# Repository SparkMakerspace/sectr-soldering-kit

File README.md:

This PCB was designed by the nerds at [Spark Makerspace](https://sparkmakerspace.org) for use with [Southeastern CT](https://southeasternctrobotics.com/) Robotics (SECTR) FLL teams in spring/summer 2023.

PCBs for 2023 were manufactured with green solder mask.
PCBs for 2024 were manufactured with blue solder mask.

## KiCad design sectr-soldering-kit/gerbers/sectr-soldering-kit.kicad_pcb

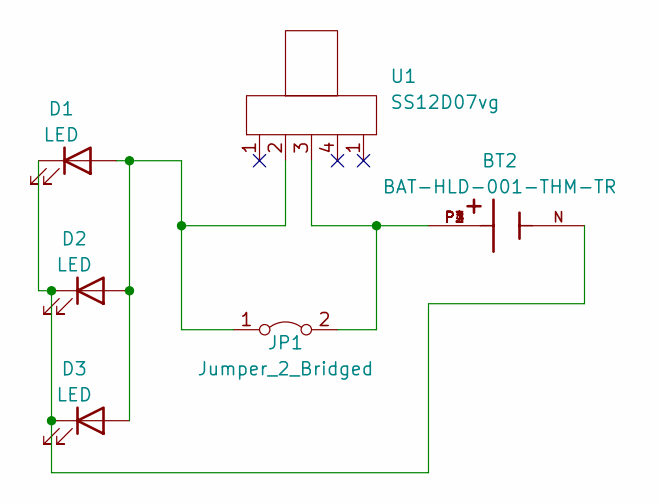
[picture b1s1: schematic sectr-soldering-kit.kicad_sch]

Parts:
BT2: BAT-HLD-001-THM-TR; BAT_BAT-HLD-001-THM-TR; PARTREV C
D1, D2, D3: LED; LED_D5.0mm
JP1: Jumper_2_Bridged; SolderJumper-2_P1.3mm_Open_TrianglePad1.0x1.5mm
U1: SS12D07vg; ss12d07vg

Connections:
unnamed: D1.2 (A), D2.2 (A), D3.2 (A), JP1.1 (A), U1.2
unnamed: BT2.N, D1.1 (K), D2.1 (K), D3.1 (K)
unnamed: BT2.P1, BT2.P2, BT2.P3, BT2.P4, JP1.2 (B), U1.3

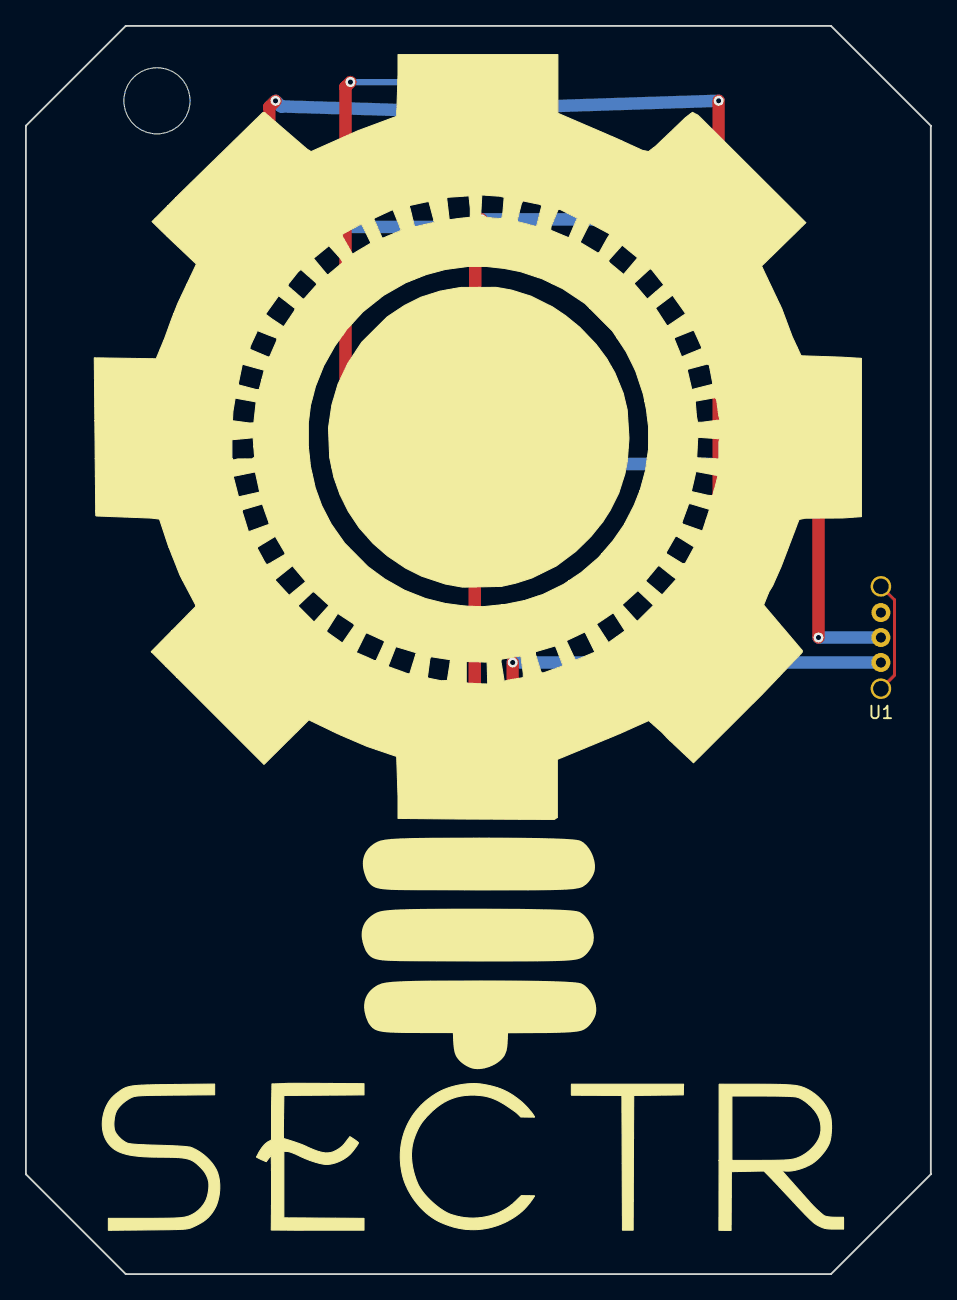
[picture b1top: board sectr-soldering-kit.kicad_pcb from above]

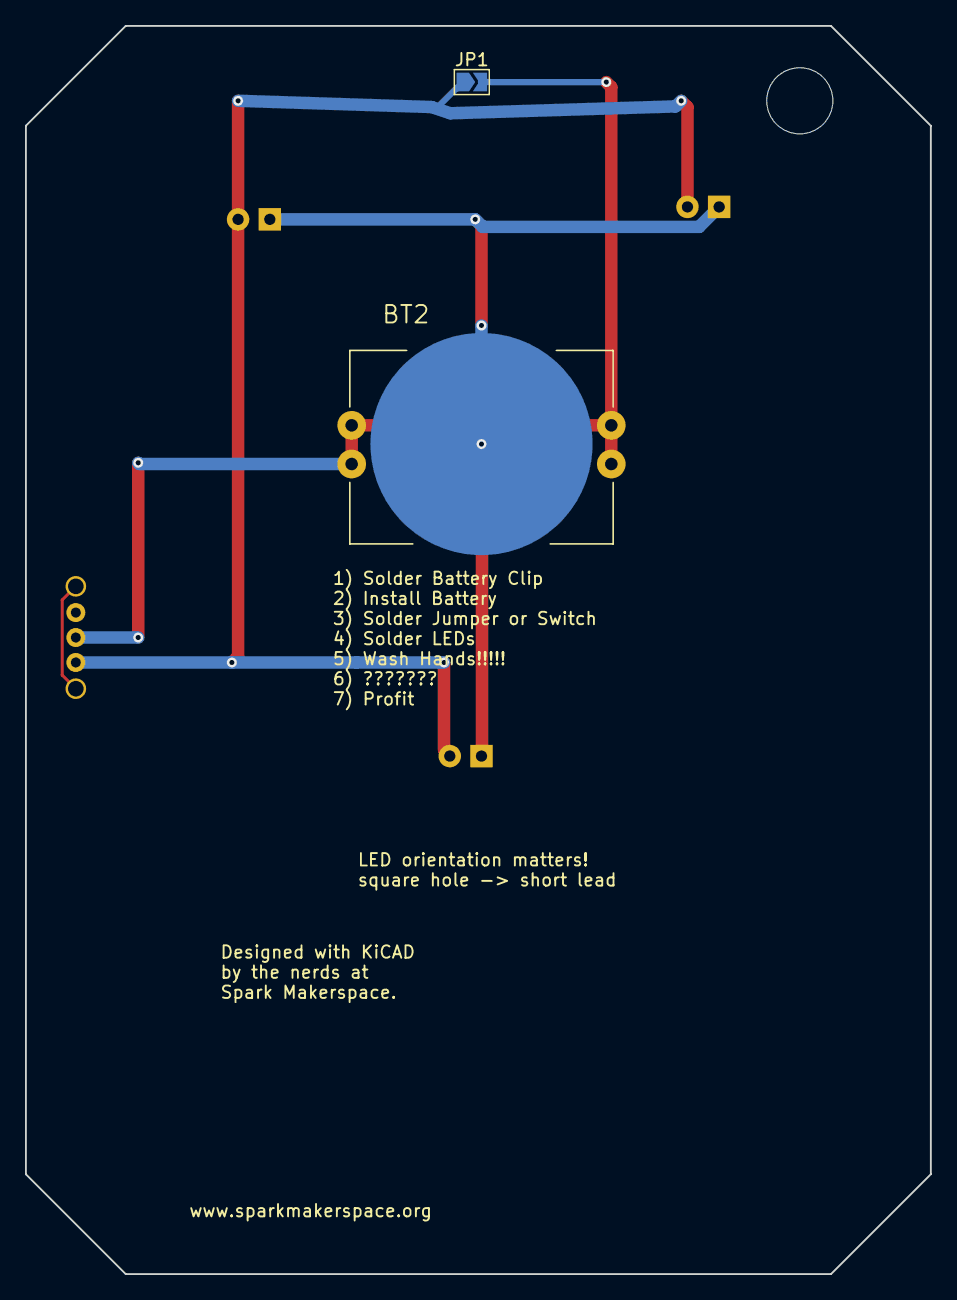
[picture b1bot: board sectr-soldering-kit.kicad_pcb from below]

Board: 2 copper layers, 72.5 x 100.0 mm, 6 parts (2 on the bottom side), 3 nets.

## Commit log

2023-06-02 initial design
2024-04-26 refactor repo and add latest
